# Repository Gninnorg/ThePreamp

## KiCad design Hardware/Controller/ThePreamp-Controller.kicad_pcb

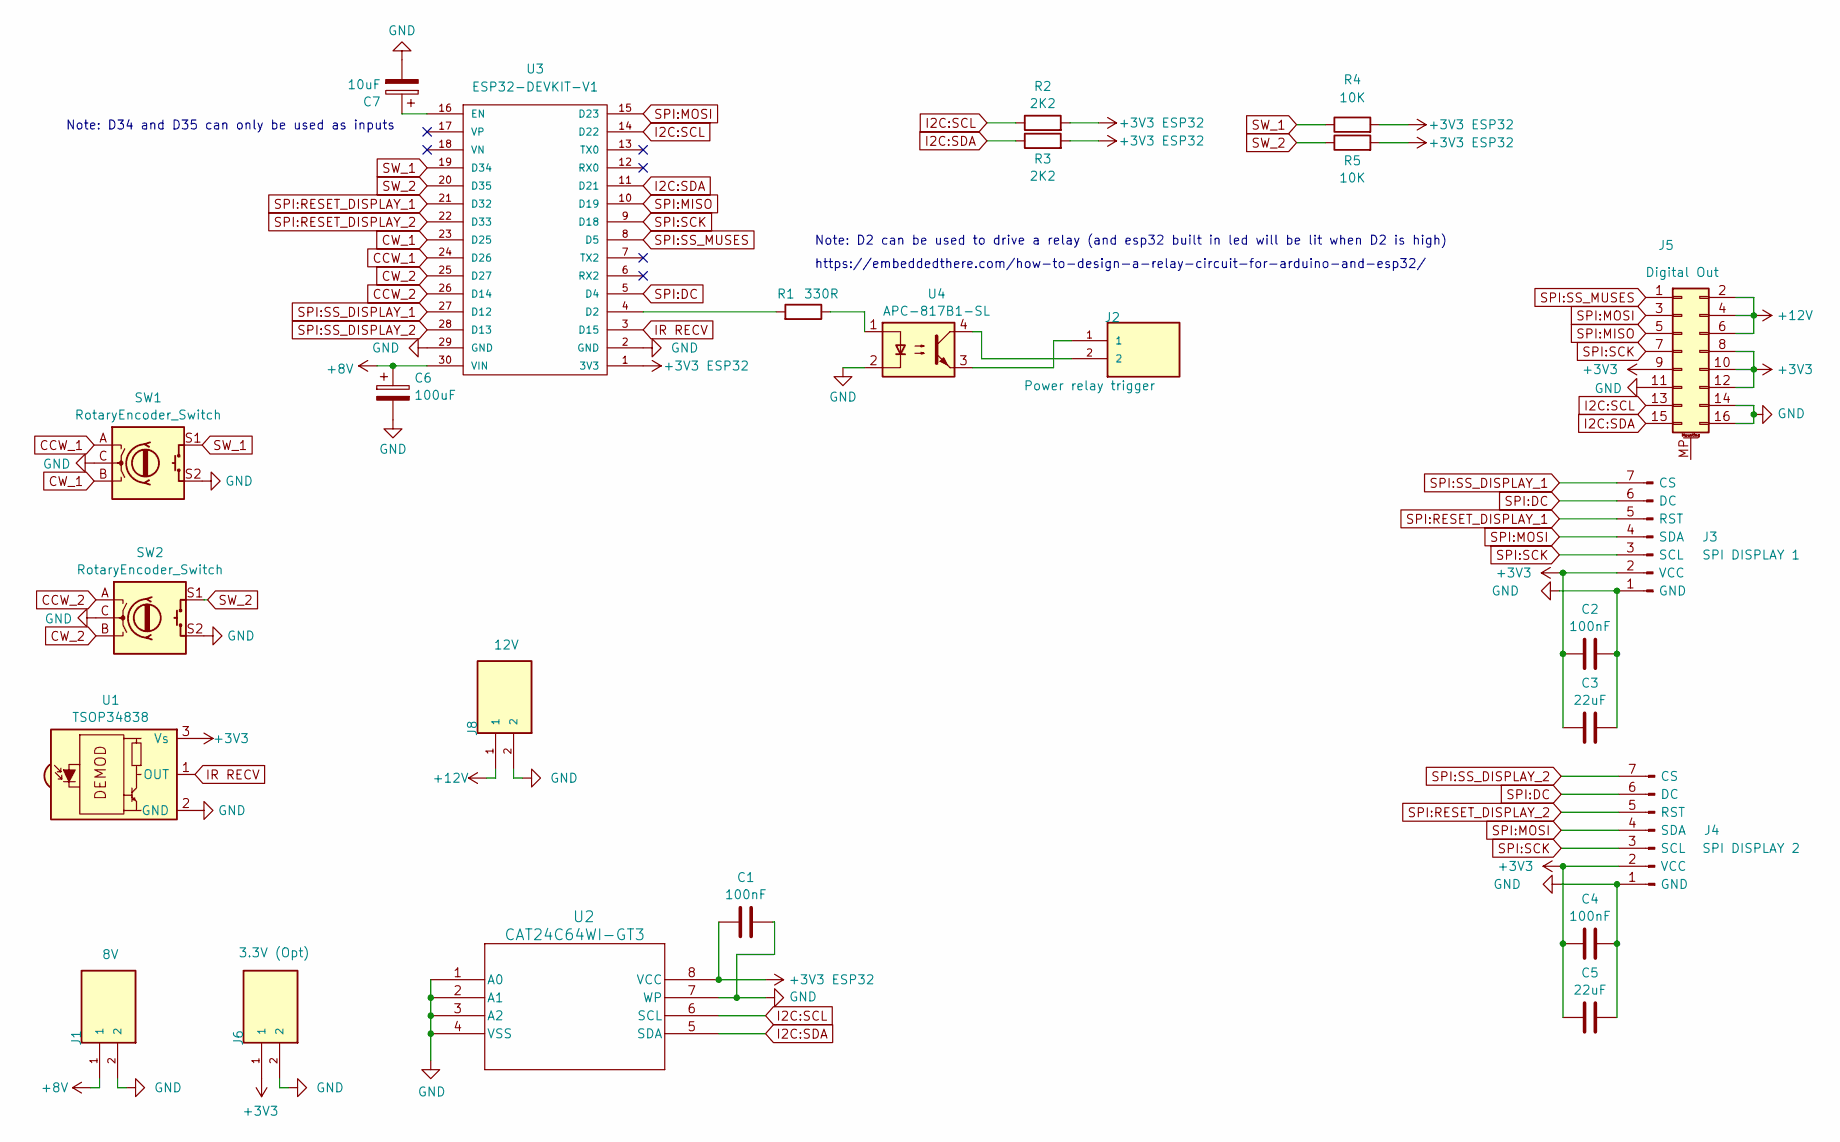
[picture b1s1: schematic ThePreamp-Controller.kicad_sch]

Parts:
C1, C2, C4: 100nF; C_0805_2012Metric_Pad1.18x1.45mm_HandSolder
C3, C5: 22uF; C_1206_3216Metric_Pad1.33x1.80mm_HandSolder
C6: 100uF; CP_Radial_D8.0mm_P3.50mm
C7: 10uF; CP_Radial_D8.0mm_P3.50mm
J1: 8V; TBP01R2-508-02BK (VERT)
J2: Power relay trigger; TBP01R2-508-02BK (VERT)
J3: SPI DISPLAY 1; OLED SPI 2.08
J4: SPI DISPLAY 2; OLED SPI 2.08
J5: Digital Out; IDC-Header_2x08_P2.54mm_Vertical
J6: 3.3V (Opt); TBP01R2-508-02BK (VERT)
J8: 12V; TBP01R2-508-02BK (VERT)
R1: 330R; R_0805_2012Metric_Pad1.20x1.40mm_HandSolder
R2, R3: 2K2; R_0805_2012Metric_Pad1.20x1.40mm_HandSolder
R4, R5: 10K; R_0805_2012Metric_Pad1.20x1.40mm_HandSolder
SW1, SW2: RotaryEncoder_Switch; RotaryEncoder_Alps_EC11E-Switch_Vertical_H20mm
U1: TSOP34838; Vishay_MOLD-3Pin
U2: CAT24C64WI-GT3; SOIC8_ONS-M
U3: ESP32-DEVKIT-V1; MODULE_ESP32_DEVKIT_V1; PARTREV N/A
U4: APC-817B1-SL; APC-817xx-SL_AMB-M

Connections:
+3V3: C2.1, C3.1, C4.1, C5.1, J3.2 (VCC), J4.2 (VCC), J5.8, J5.9, J5.10, J5.12, J6.1, U1.3 (Vs)
+3V3 ESP32: C1.1, R2.2, R3.2, R4.2, R5.2, U2.8 (VCC), U3.1 (3V3)
+8V: C6.1, J1.1, U3.30 (VIN)
+12V: J5.2, J5.4, J5.6, J8.1
CCW_1: SW1.A, U3.24 (D26)
CCW_2: SW2.A, U3.26 (D14)
CW_1: SW1.B, U3.23 (D25)
CW_2: SW2.B, U3.25 (D27)
GND: C1.2, C2.2, C3.2, C4.2, C5.2, C6.2, C7.2, J1.2, J3.1 (GND), J4.1 (GND), J5.11, J5.14, J5.16, J6.2, J8.2, SW1.C, SW1.S2, SW2.C, SW2.S2, U1.2 (GND), U2.1 (A0), U2.2 (A1), U2.3 (A2), U2.4 (VSS), U2.7 (WP), U3.2 (GND), U3.29 (GND), U4.2
I2C:SCL: J5.13, R2.1, U2.6 (SCL), U3.14 (D22)
I2C:SDA: J5.15, R3.1, U2.5 (SDA), U3.11 (D21)
IR RECV: U1.1 (OUT), U3.3 (D15)
unnamed: J2.1, U4.3
unnamed: J2.2, U4.4
unnamed: R1.1, U4.1
unnamed: R1.2, U3.4 (D2)
unnamed: C7.1, U3.16 (EN)
SPI:DC: J3.6 (DC), J4.6 (DC), U3.5 (D4)
SPI:MISO: J5.5, U3.10 (D19)
SPI:MOSI: J3.4 (SDA), J4.4 (SDA), J5.3, U3.15 (D23)
SPI:RESET_DISPLAY_1: J3.5 (RST), U3.21 (D32)
SPI:RESET_DISPLAY_2: J4.5 (RST), U3.22 (D33)
SPI:SCK: J3.3 (SCL), J4.3 (SCL), J5.7, U3.9 (D18)
SPI:SS_DISPLAY_1: J3.7 (CS), U3.27 (D12)
SPI:SS_DISPLAY_2: J4.7 (CS), U3.28 (D13)
SPI:SS_MUSES: J5.1, U3.8 (D5)
SW_1: R4.1, SW1.S1, U3.19 (D34)
SW_2: R5.1, SW2.S1, U3.20 (D35)

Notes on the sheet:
Note: D34 and D35 can only be used as inputs
https://embeddedthere.com/how-to-design-a-relay-circuit-for-arduino-and-esp32/
Note: D2 can be used to drive a relay (and esp32 built in led will be lit when D2 is high)

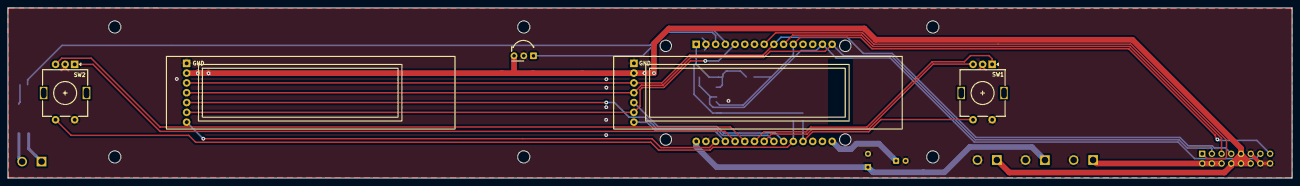
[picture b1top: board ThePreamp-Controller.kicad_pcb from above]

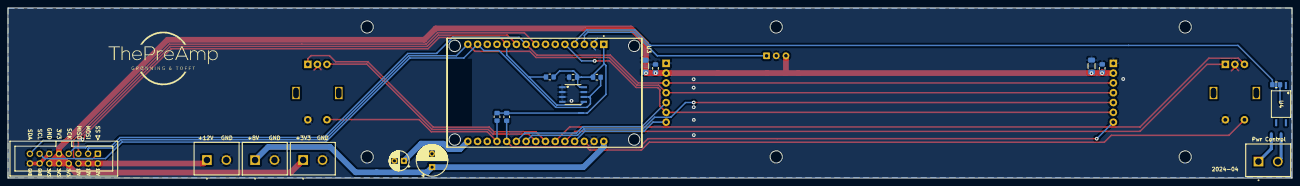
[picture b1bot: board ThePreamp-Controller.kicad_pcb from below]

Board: 2 copper layers, 335.9 x 44.5 mm, 31 parts (20 on the bottom side), 28 nets.

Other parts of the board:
 : MountingHole_3.2mm_M3_ISO7380
 #2,  #3,  #4,  #5,  #6: MountingHole_3.2mm_M3_ISO7380

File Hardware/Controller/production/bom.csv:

Designator,Footprint,Quantity,Value,LCSC Part #
"C1, C2, C4",0805,3,100nF,
"C3, C5",1206,2,22uF,
C6,CP_Radial_D8.0mm_P3.50mm,1,100uF,
J1,TBP01R2-508-02BK (VERT),1,8V,
J2,TBP01R2-508-02BK (VERT),1,Power relay trigger,
J3,OLED SPI 2.08,1,SPI DISPLAY 1,
J4,OLED SPI 2.08,1,SPI DISPLAY 2,
J5,IDC-Header_2x08_P2.54mm_Vertical,1,Digital Out,
J6,TBP01R2-508-02BK (VERT),1,3.3V (Opt),
J8,TBP01R2-508-02BK (VERT),1,12V,
R1,0805,1,330R,
"R2, R3",0805,2,2K2,
"SW1, SW2",RotaryEncoder_Alps_EC11E-Switch_Vertical_H20mm,2,RotaryEncoder_Switch,
U1,Vishay_MOLD-3Pin,1,TSOP34838,
U2,SOIC8_ONS-M,1,CAT24C64WI-GT3,
U3,MODULE_ESP32_DEVKIT_V1,1,ESP32-DEVKIT-V1,
U4,DIP-4_W7.62mm,1,APC-817B1-SL,

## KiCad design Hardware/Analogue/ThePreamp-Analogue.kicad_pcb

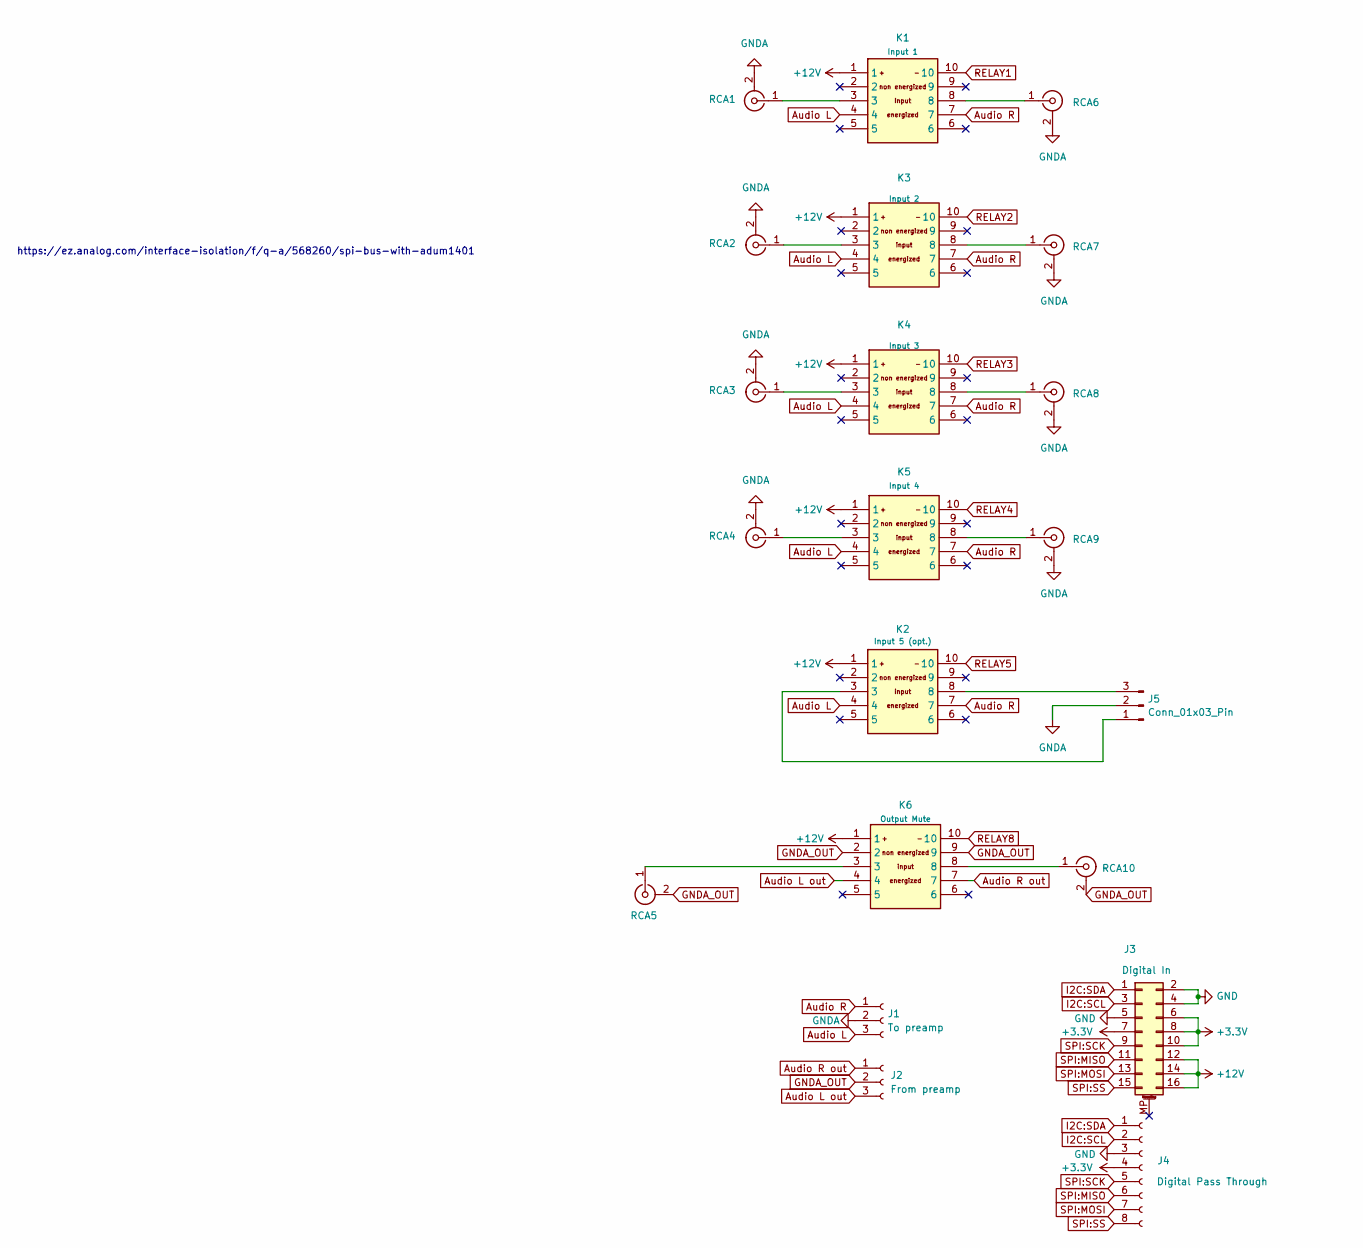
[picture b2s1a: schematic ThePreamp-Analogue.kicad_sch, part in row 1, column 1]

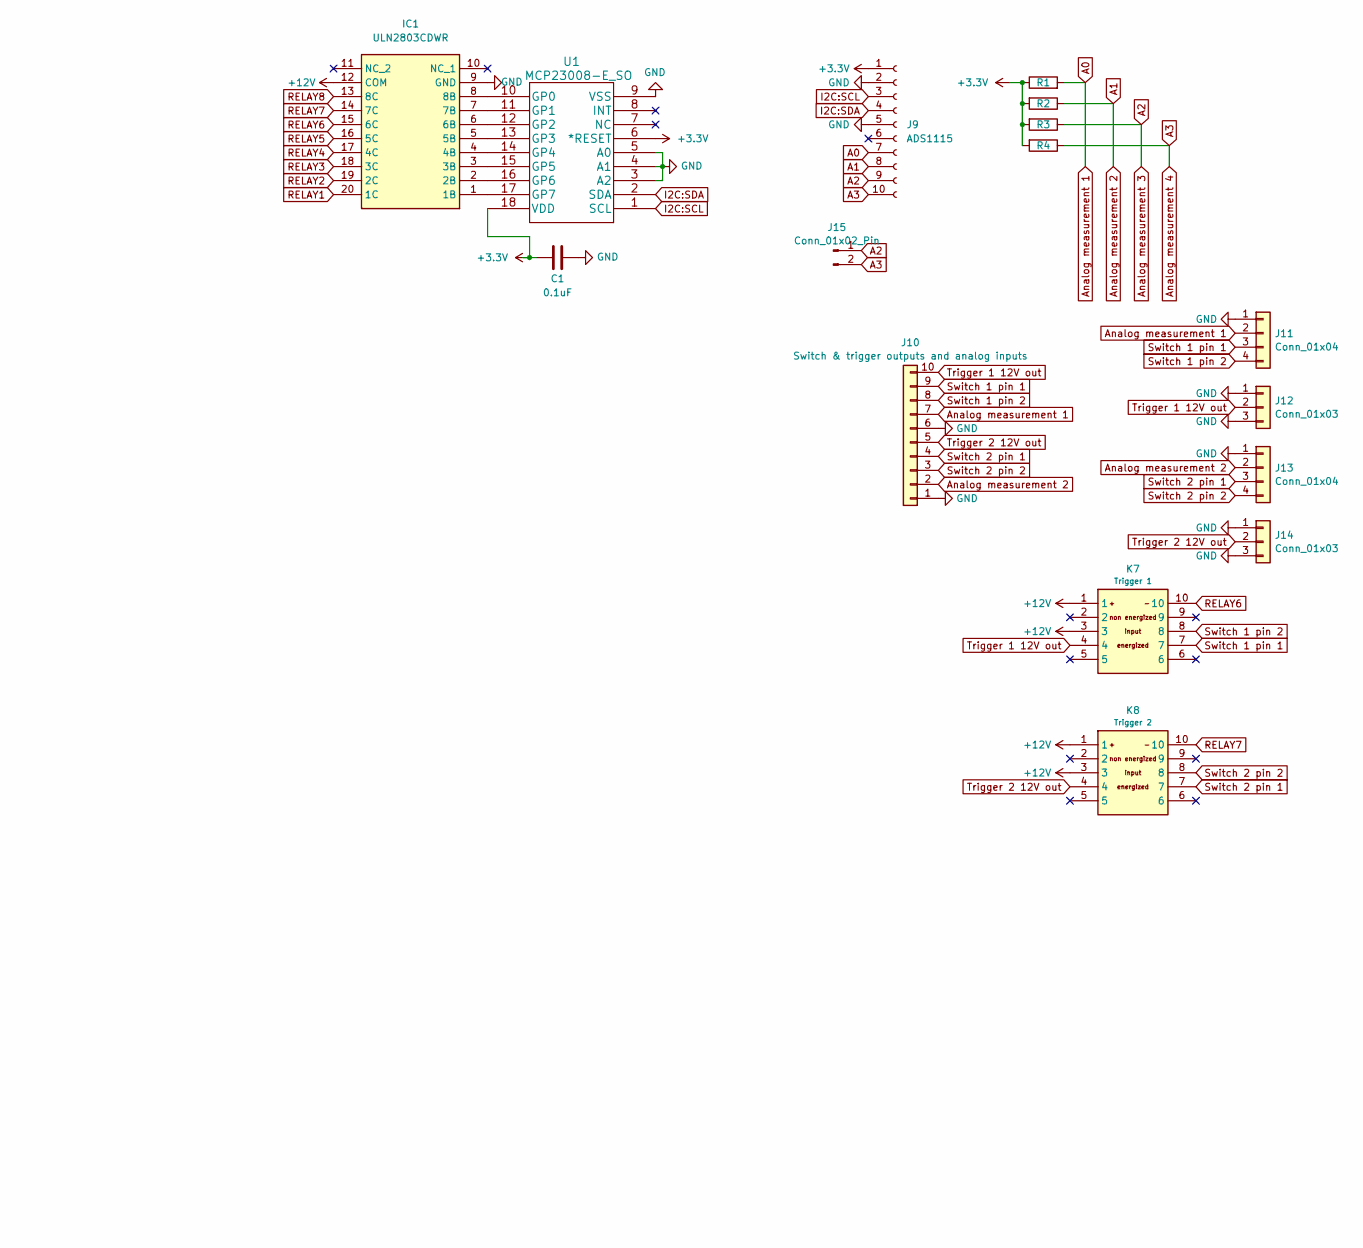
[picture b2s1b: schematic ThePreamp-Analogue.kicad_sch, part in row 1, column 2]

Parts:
C1: 0.1uF; C_0805_2012Metric_Pad1.18x1.45mm_HandSolder
IC1: ULN2803CDWR; SOIC127P1030X265-20N; Mouser Part Number 595-ULN2803CDWR
J1: To preamp; PinSocket_1x03_P2.54mm_Vertical
J2: From preamp; PinSocket_1x03_P2.54mm_Vertical
J3: Digital In; IDC-Header_2x08_P2.54mm_Vertical
J4: Digital Pass Through; PinSocket_1x08_P2.54mm_Vertical
J5: Conn_01x03_Pin; PinHeader_1x03_P2.54mm_Vertical
J9: ADS1115; PinHeader_1x10_P2.54mm_Vertical
J10: Switch & trigger outputs and analog inputs; PinSocket_1x10_P2.54mm_Vertical
J11, J13: Conn_01x04; M8 4 pin
J12, J14: Conn_01x03; M8 3 pin
J15: Conn_01x02_Pin; PinHeader_1x02_P2.54mm_Vertical
K1: Input 1; DIPS762W60P254L1420H630Q10N; Manufacturer_Part_Number EA2-12NJ; Mouser Part Number 551-EA2-12NJ
K2: Input 5 (opt.); DIPS762W60P254L1420H630Q10N; Manufacturer_Part_Number EA2-12NJ; Mouser Part Number 551-EA2-12NJ
K3: Input 2; DIPS762W60P254L1420H630Q10N; Manufacturer_Part_Number EA2-12NJ; Mouser Part Number 551-EA2-12NJ
K4: Input 3; DIPS762W60P254L1420H630Q10N; Manufacturer_Part_Number EA2-12NJ; Mouser Part Number 551-EA2-12NJ
K5: Input 4; DIPS762W60P254L1420H630Q10N; Manufacturer_Part_Number EA2-12NJ; Mouser Part Number 551-EA2-12NJ
K6: Output Mute; DIPS762W60P254L1420H630Q10N; Manufacturer_Part_Number EA2-12NJ; Mouser Part Number 551-EA2-12NJ
K7: Trigger 1; DIPS762W60P254L1420H630Q10N; Manufacturer_Part_Number EA2-12NJ; Mouser Part Number 551-EA2-12NJ
K8: Trigger 2; DIPS762W60P254L1420H630Q10N; Manufacturer_Part_Number EA2-12NJ; Mouser Part Number 551-EA2-12NJ
R1, R2, R3, R4: 10K; R_0805_2012Metric_Pad1.20x1.40mm_HandSolder
RCA1, RCA2, RCA3, RCA4, RCA5, RCA6, RCA7, RCA8, RCA9, RCA10: RCA_Connector_ALI; RCA Connector ALI
U1: MCP23008-E_SO; SOIC127P1030X265-18N

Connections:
+3.3V: C1.1, J3.6, J3.7, J3.8, J3.10, J4.4, J9.1, R1.1, R2.2, R3.2, R4.2, U1.6 (*RESET), U1.18 (VDD)
+12V: IC1.12 (COM), J3.12, J3.14, J3.16, K1.1, K2.1, K3.1, K4.1, K5.1, K6.1, K7.1, K7.3, K8.1, K8.3
A0: J9.7, J10.7, J11.2, R1.2
A1: J9.8, J10.2, J13.2, R2.1
A2: J9.9, J15.1, R3.1
A3: J9.10, J15.2, R4.1
Audio L: J1.3, K1.4, K2.4, K3.4, K4.4, K5.4
Audio L out: J2.3, K6.4
Audio R: J1.1, K1.7, K2.7, K3.7, K4.7, K5.7
Audio R out: J2.1, K6.7
GND: C1.2, IC1.9 (GND), J3.2, J3.4, J3.5, J4.3, J9.2, J9.5, J10.1, J10.6, J11.1, J12.1, J12.3, J13.1, J14.1, J14.3, U1.3 (A2), U1.4 (A1), U1.5 (A0), U1.9 (VSS)
GNDA: J1.2, J5.2, RCA1.2 (Ext), RCA2.2 (Ext), RCA3.2 (Ext), RCA4.2 (Ext), RCA6.2 (Ext), RCA7.2 (Ext), RCA8.2 (Ext), RCA9.2 (Ext)
GNDA_OUT: J2.2, K6.2, K6.9, RCA5.2 (Ext), RCA10.2 (Ext)
I2C:SCL: J3.3, J4.2, J9.3, U1.1 (SCL)
I2C:SDA: J3.1, J4.1, J9.4, U1.2 (SDA)
unnamed: IC1.1 (1B), U1.17 (GP7)
unnamed: IC1.2 (2B), U1.16 (GP6)
unnamed: IC1.3 (3B), U1.15 (GP5)
unnamed: IC1.4 (4B), U1.14 (GP4)
unnamed: IC1.5 (5B), U1.13 (GP3)
unnamed: IC1.6 (6B), U1.12 (GP2)
unnamed: IC1.7 (7B), U1.11 (GP1)
unnamed: IC1.8 (8B), U1.10 (GP0)
unnamed: J5.1, K2.3
unnamed: J5.3, K2.8
unnamed: K1.3, RCA1.1 (In)
unnamed: K3.3, RCA2.1 (In)
unnamed: K4.3, RCA3.1 (In)
unnamed: K5.3, RCA4.1 (In)
unnamed: K6.3, RCA5.1 (In)
unnamed: K1.8, RCA6.1 (In)
unnamed: K3.8, RCA7.1 (In)
unnamed: K4.8, RCA8.1 (In)
unnamed: K5.8, RCA9.1 (In)
unnamed: K6.8, RCA10.1 (In)
RELAY1: IC1.20 (1C), K1.10
RELAY2: IC1.19 (2C), K3.10
RELAY3: IC1.18 (3C), K4.10
RELAY4: IC1.17 (4C), K5.10
RELAY5: IC1.16 (5C), K2.10
RELAY6: IC1.15 (6C), K7.10
RELAY7: IC1.14 (7C), K8.10
RELAY8: IC1.13 (8C), K6.10
SPI:MISO: J3.11, J4.6
SPI:MOSI: J3.13, J4.7
SPI:SCK: J3.9, J4.5
SPI:SS: J3.15, J4.8
Switch 1 pin 1: J10.9, J11.3, K7.7
Switch 1 pin 2: J10.8, J11.4, K7.8
Switch 2 pin 1: J10.4, J13.3, K8.7
Switch 2 pin 2: J10.3, J13.4, K8.8
Trigger 1 12V out: J10.10, J12.2, K7.4
Trigger 2 12V out: J10.5, J14.2, K8.4

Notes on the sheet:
https://ez.analog.com/interface-isolation/f/q-a/568260/spi-bus-with-adum1401

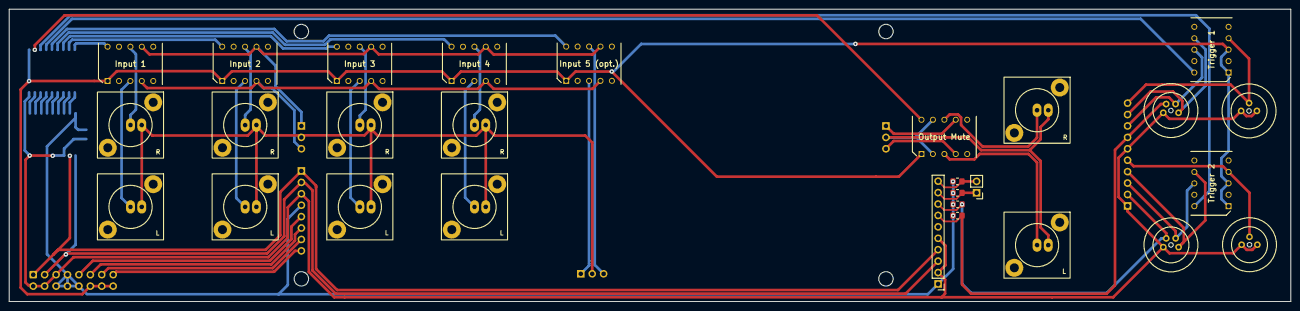
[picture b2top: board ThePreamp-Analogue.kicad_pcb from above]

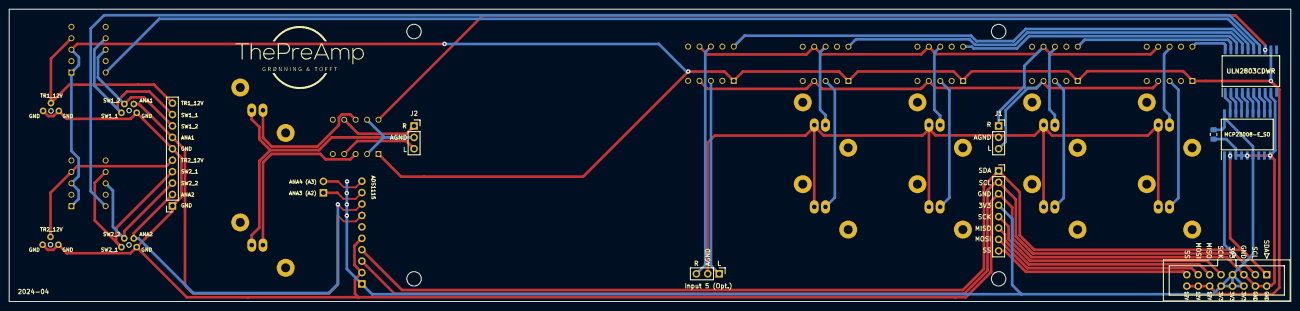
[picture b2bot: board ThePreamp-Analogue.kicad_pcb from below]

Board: 2 copper layers, 285.0 x 65.0 mm, 37 parts (9 on the bottom side), 53 nets.

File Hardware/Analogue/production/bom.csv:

Designator,Footprint,Quantity,Value,LCSC Part #
C1,0805,1,0.1uF,
IC1,SOIC127P1030X265-20N,1,ULN2803CDWR,
J1,PinSocket_1x03_P2.54mm_Vertical,1,To preamp,
J10,PinSocket_1x10_P2.54mm_Vertical,1,Switch & trigger outputs and analog inputs,
"J11, J13",M8 4 pin,2,Conn_01x04,
"J12, J14",M8 3 pin,2,Conn_01x03,
J15,PinHeader_1x02_P2.54mm_Vertical,1,Conn_01x02_Pin,
J2,PinSocket_1x03_P2.54mm_Vertical,1,From preamp,
J3,IDC-Header_2x08_P2.54mm_Vertical,1,Digital In,
J4,PinSocket_1x08_P2.54mm_Vertical,1,Digital Pass Through,
J5,PinHeader_1x03_P2.54mm_Vertical,1,Conn_01x03_Pin,
J9,PinHeader_1x10_P2.54mm_Vertical,1,ADS1115,
K1,DIPS762W60P254L1420H630Q10N,1,Input 1,
K2,DIPS762W60P254L1420H630Q10N,1,Input 5 (opt.),
K3,DIPS762W60P254L1420H630Q10N,1,Input 2,
K4,DIPS762W60P254L1420H630Q10N,1,Input 3,
K5,DIPS762W60P254L1420H630Q10N,1,Input 4,
K6,DIPS762W60P254L1420H630Q10N,1,Output Mute,
K7,DIPS762W60P254L1420H630Q10N,1,Trigger 1,
K8,DIPS762W60P254L1420H630Q10N,1,Trigger 2,
"R1, R2, R3, R4",0805,4,10K,
"RCA1, RCA10, RCA2, RCA3, RCA4, RCA5, RCA6, RCA7, RCA8, RCA9",RCA Connector ALI,10,RCA_Connector_ALI,
U1,SOIC127P1030X265-18N,1,MCP23008-E_SO,

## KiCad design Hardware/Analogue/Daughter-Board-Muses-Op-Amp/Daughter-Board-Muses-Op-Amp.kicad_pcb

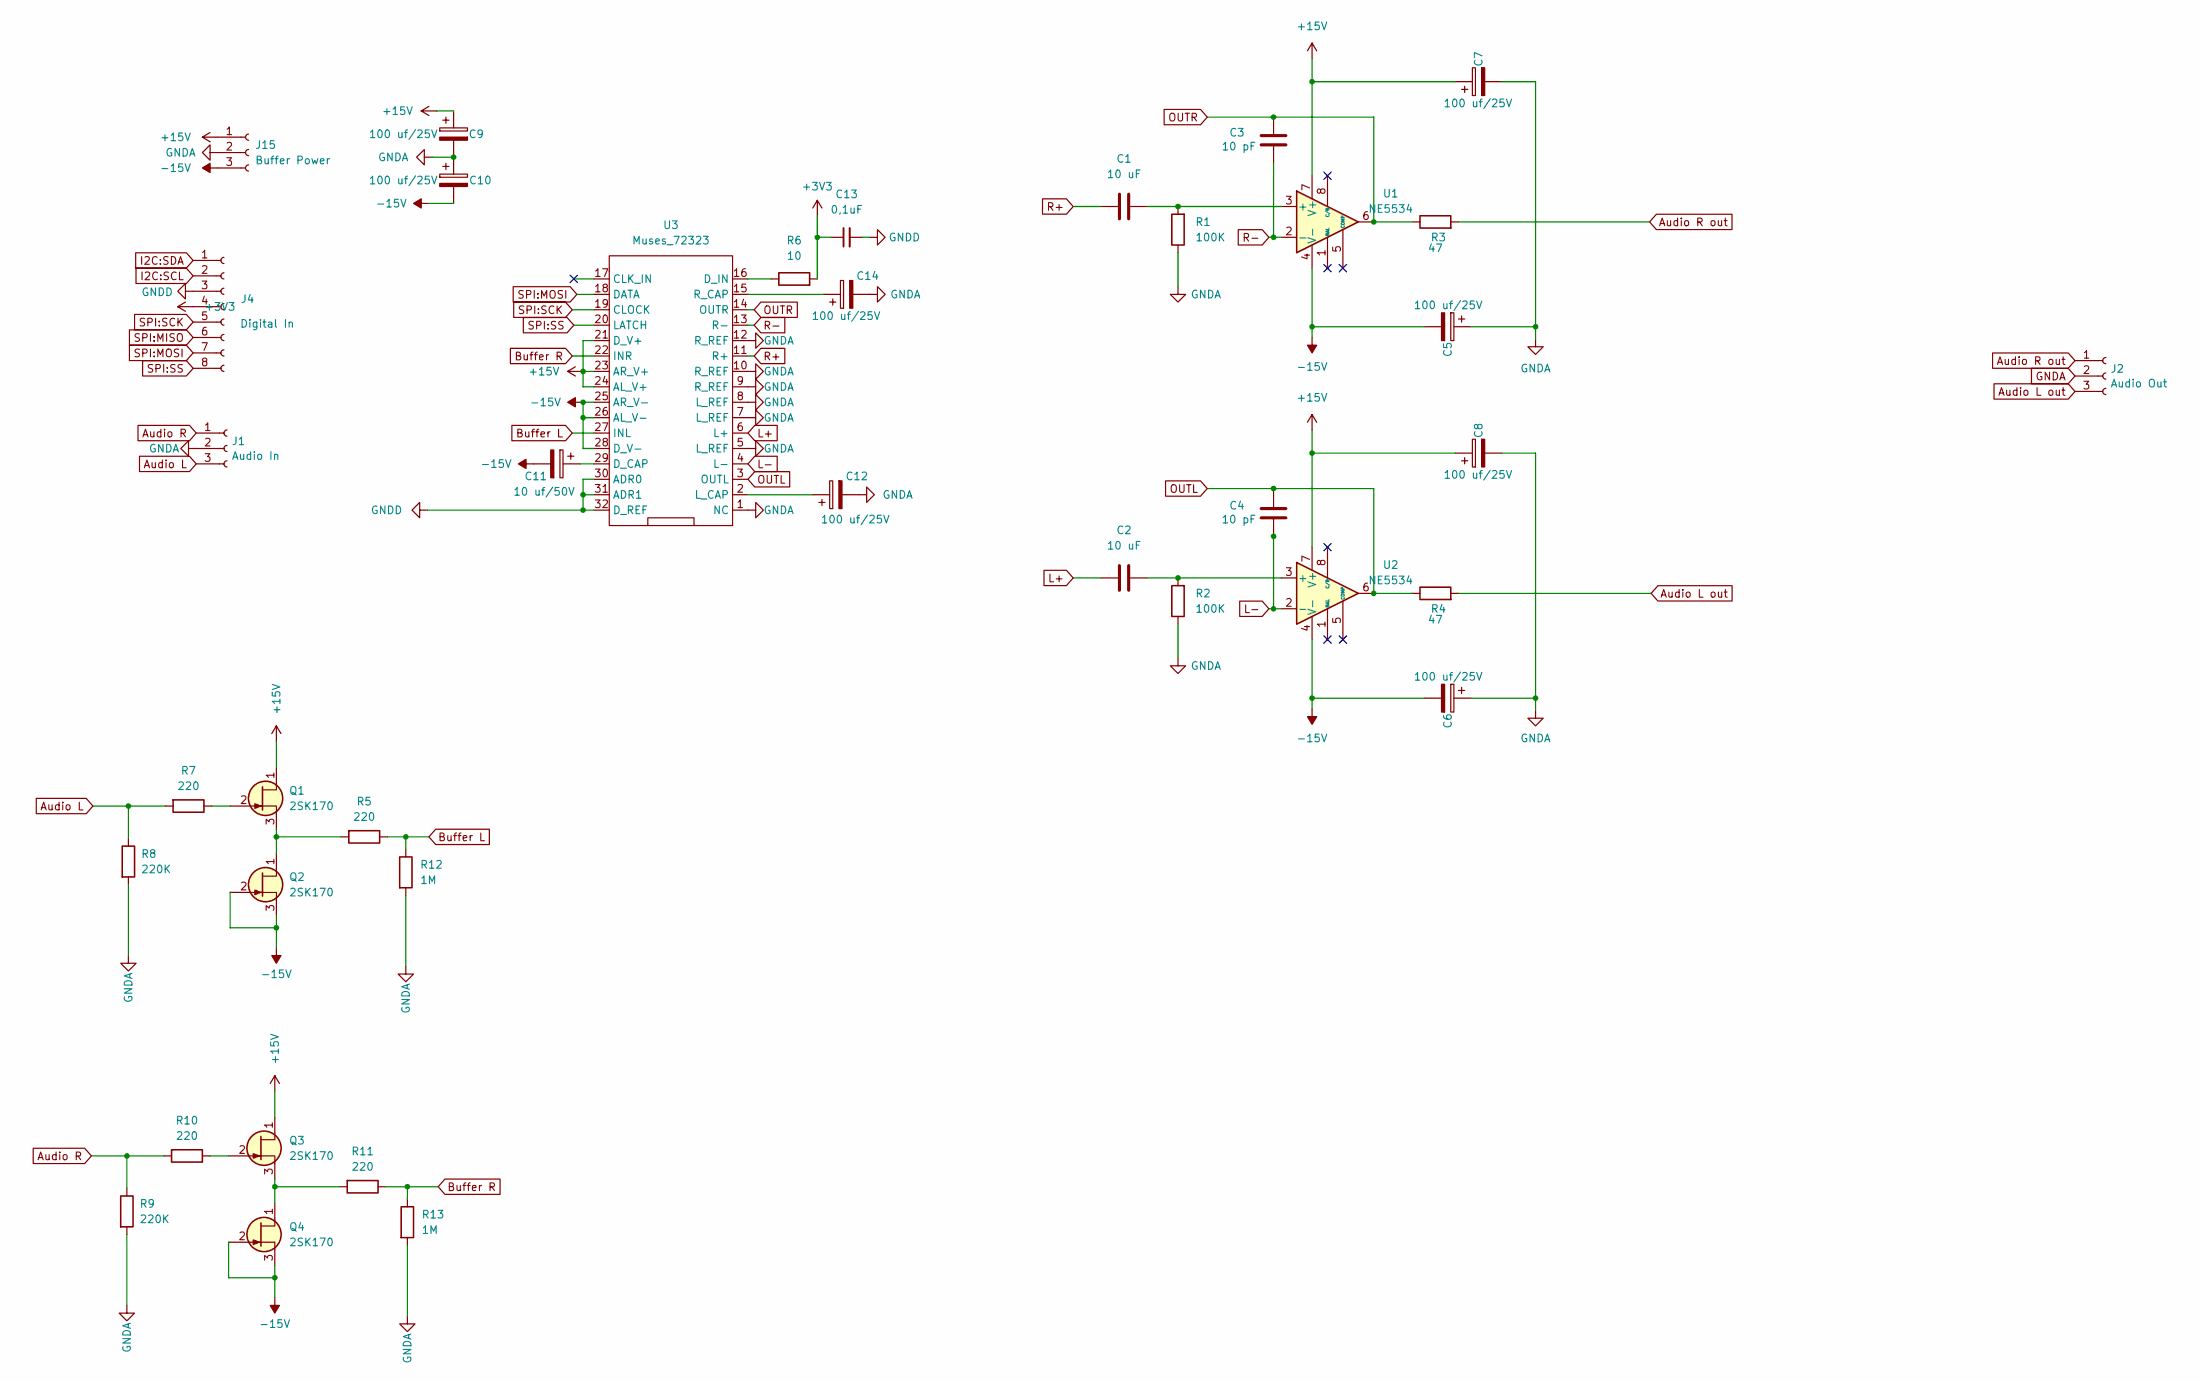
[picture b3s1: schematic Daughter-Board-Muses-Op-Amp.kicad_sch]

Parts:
C1, C2: 10 uF; CP_Radial_D5.0mm_P2.00mm
C3, C4: 10 pF; C_0805_2012Metric_Pad1.18x1.45mm_HandSolder
C5, C6, C7, C8, C9, C10, C12, C14: 100 uf/25V; CP_Radial_D8.0mm_P3.50mm
C11: 10 uf/50V; CP_Radial_D5.0mm_P2.00mm
C13: 0,1uF; C_0805_2012Metric_Pad1.18x1.45mm_HandSolder
J1: Audio In; PinHeader_1x03_P2.54mm_Vertical
J2: Audio Out; PinHeader_1x03_P2.54mm_Vertical
J4: Digital In; PinHeader_1x08_P2.54mm_Vertical
J15: Buffer Power; PinHeader_1x03_P2.54mm_Vertical
Q1, Q2, Q3, Q4: 2SK170; TO-92_HandSolder
R1, R2: 100K; R_0805_2012Metric_Pad1.20x1.40mm_HandSolder
R3, R4: 47; R_0805_2012Metric_Pad1.20x1.40mm_HandSolder
R5, R7, R10, R11: 220; R_0805_2012Metric_Pad1.20x1.40mm_HandSolder
R6: 10; R_0805_2012Metric_Pad1.20x1.40mm_HandSolder
R8, R9: 220K; R_0805_2012Metric_Pad1.20x1.40mm_HandSolder
R12, R13: 1M; R_0805_2012Metric_Pad1.20x1.40mm_HandSolder
U1, U2: NE5534; DIP-8_W7.62mm_Socket_LongPads
U3: Muses_72323; TSSOP-32_6.1x11mm_P0.65mm

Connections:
+3V3: C13.1, J4.4, R6.2
+15V: C7.1, C8.1, C9.1, J15.1, Q1.1 (D), Q3.1 (D), U1.7 (V+), U2.7 (V+), U3.21 (D_V+), U3.23 (AR_V+), U3.24 (AL_V+)
-15V: C5.2, C6.2, C10.2, C11.2, J15.3, Q2.2 (G), Q2.3 (S), Q4.2 (G), Q4.3 (S), U1.4 (V-), U2.4 (V-), U3.25 (AR_V-), U3.26 (AL_V-), U3.28 (D_V-)
Audio L: J1.3, R7.2, R8.1
Audio L out: J2.3, R4.2
Audio R: J1.1, R9.1, R10.2
Audio R out: J2.1, R3.2
Buffer L: R5.1, R12.1, U3.27 (INL)
Buffer R: R11.1, R13.1, U3.22 (INR)
GNDA: C5.1, C6.1, C7.2, C8.2, C9.2, C10.1, C12.2, C14.2, J1.2, J2.2, J15.2, R1.1, R2.1, R8.2, R9.2, R12.2, R13.2, U3.1 (NC), U3.5 (L_REF), U3.7 (L_REF), U3.8 (L_REF), U3.9 (R_REF), U3.10 (R_REF), U3.12 (R_REF)
GNDD: C13.2, J4.3, U3.30 (ADR0), U3.31 (ADR1), U3.32 (D_REF)
I2C:SCL: J4.2
I2C:SDA: J4.1
L+: C2.1, U3.6 (L+)
L-: C4.2, U2.2 (-), U3.4 (L-)
unnamed: Q1.2 (G), R7.1
unnamed: Q1.3 (S), Q2.1 (D), R5.2
unnamed: Q3.2 (G), R10.1
unnamed: Q3.3 (S), Q4.1 (D), R11.2
unnamed: C1.2, R1.2, U1.3 (+)
unnamed: C2.2, R2.2, U2.3 (+)
unnamed: C11.1, U3.29 (D_CAP)
unnamed: R6.1, U3.16 (D_IN)
unnamed: C12.1, U3.2 (L_CAP)
unnamed: C14.1, U3.15 (R_CAP)
OUTL: C4.1, R4.1, U2.6, U3.3 (OUTL)
OUTR: C3.1, R3.1, U1.6, U3.14 (OUTR)
R+: C1.1, U3.11 (R+)
R-: C3.2, U1.2 (-), U3.13 (R-)
SPI:MISO: J4.6
SPI:MOSI: J4.7, U3.18 (DATA)
SPI:SCK: J4.5, U3.19 (CLOCK)
SPI:SS: J4.8, U3.20 (LATCH)

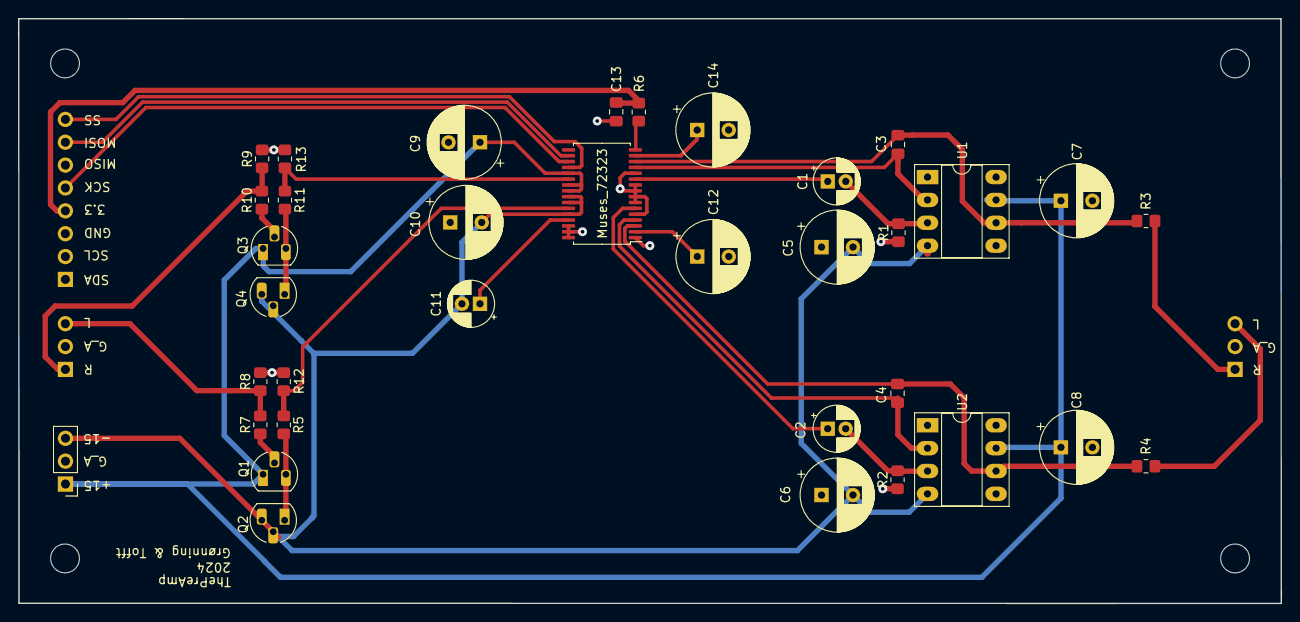
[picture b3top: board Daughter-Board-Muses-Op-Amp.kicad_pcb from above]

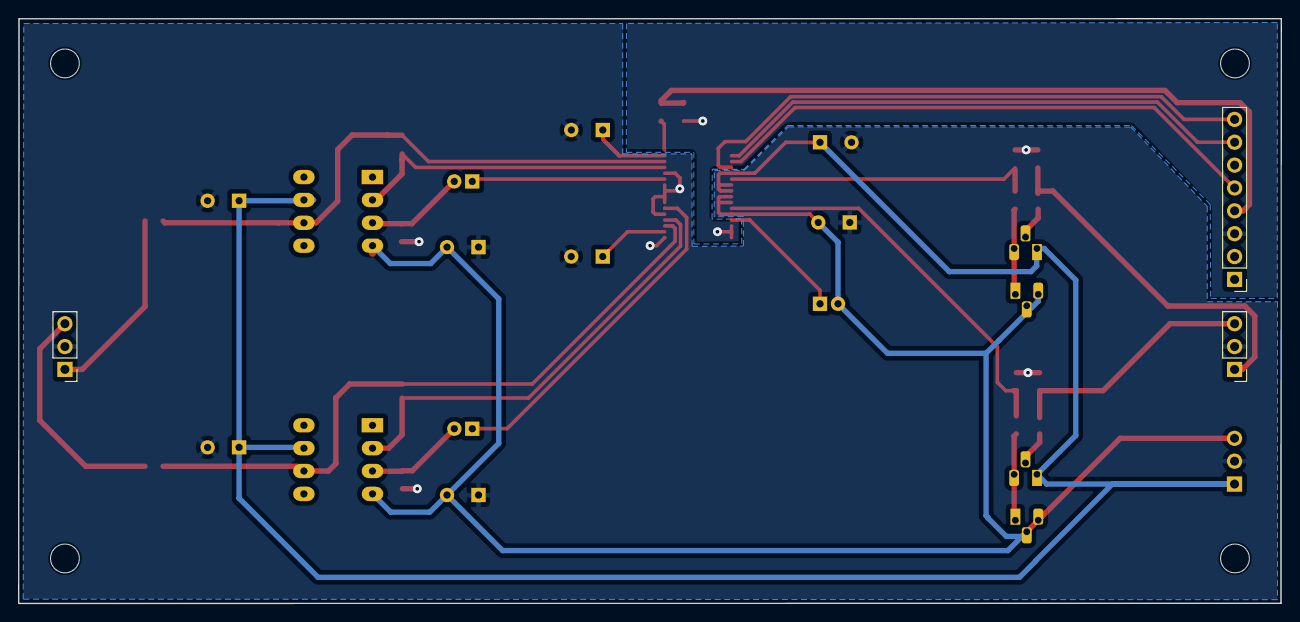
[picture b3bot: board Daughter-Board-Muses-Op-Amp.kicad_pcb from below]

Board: 2 copper layers, 140.3 x 65.0 mm, 38 parts (3 on the bottom side), 30 nets.

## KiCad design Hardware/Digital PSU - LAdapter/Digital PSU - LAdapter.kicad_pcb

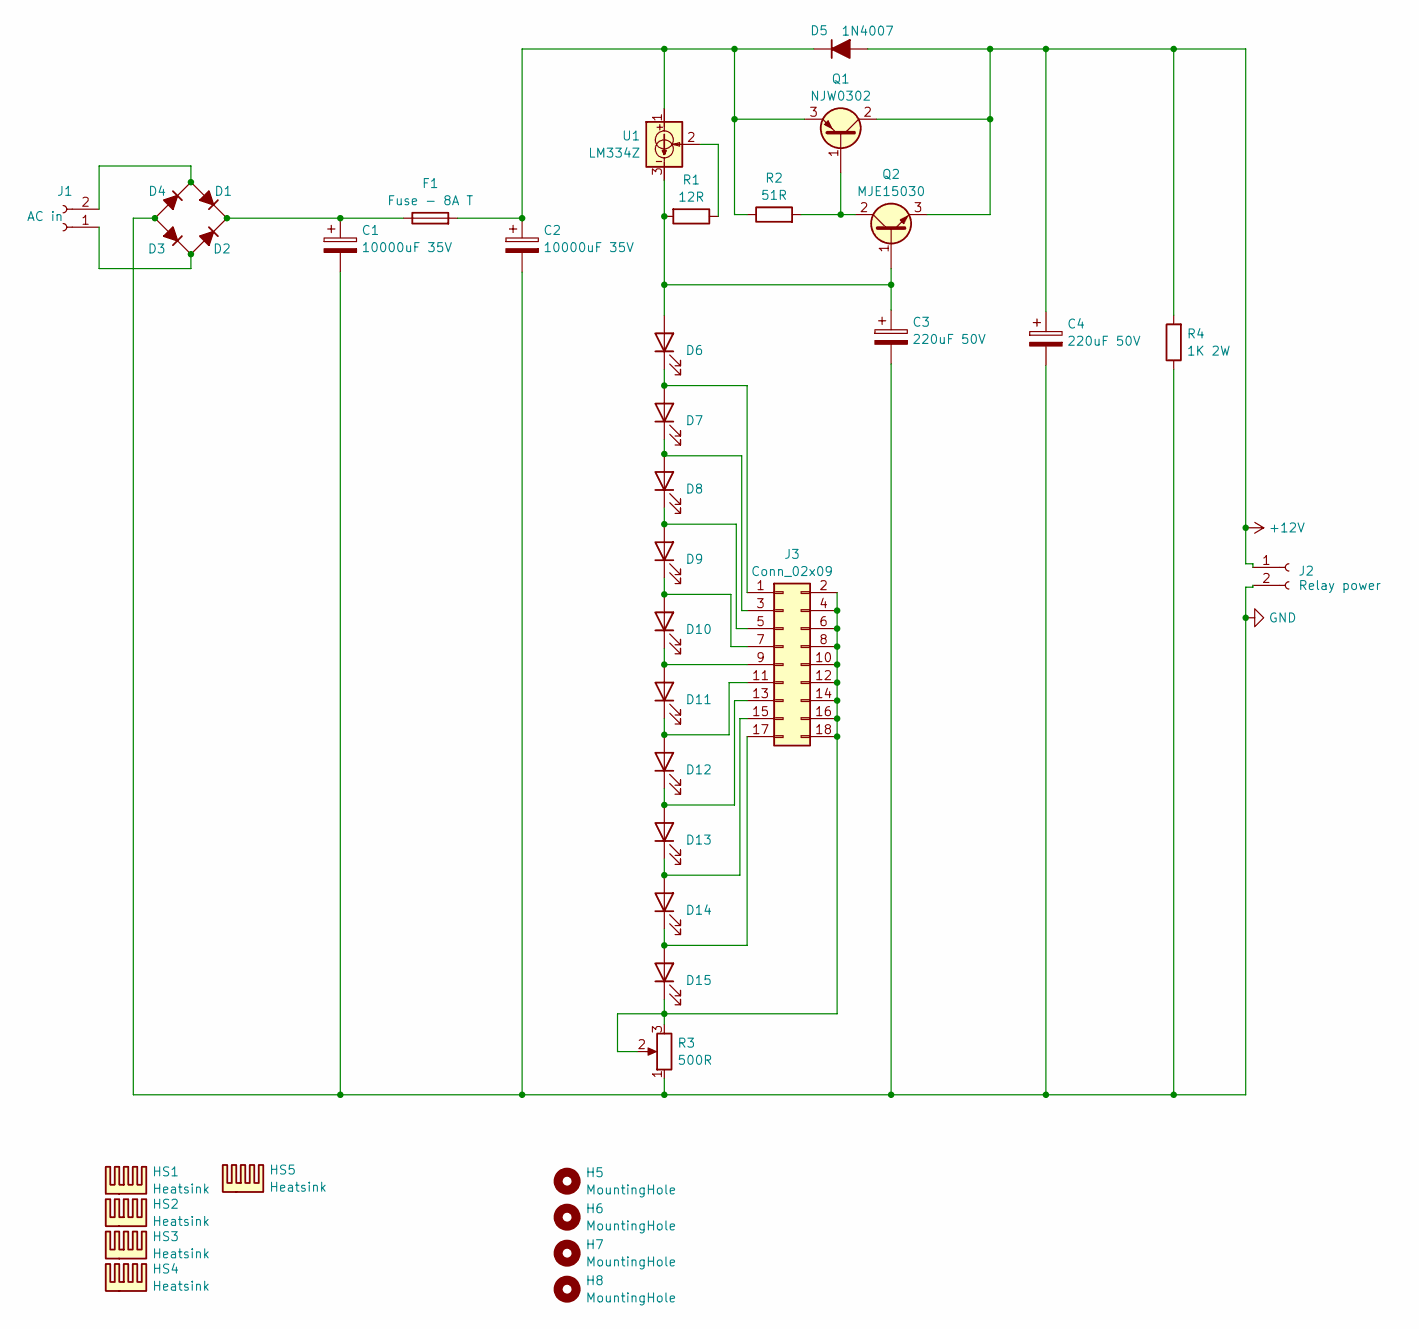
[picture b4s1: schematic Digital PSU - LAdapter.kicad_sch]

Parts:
C1, C2: 10000uF 35V; CP_Radial_D30.0mm_P10.00mm_SnapIn
C3, C4: 220uF 50V; CP_Radial_D10.0mm_P5.00mm
D1, D2, D3, D4: D_45deg_Filled; TO-220-2_Vertical
D5: 1N4007; D_DO-41_SOD81_P7.62mm_Horizontal
D6, D7, D8, D9, D10, D11, D12, D13, D14, D15: LED_Rectangular_W5.0mm_H2.0mm
F1: Fuse - 8A T; Keystone fuseholder 4527
H5, H6, H7, H8: MountingHole; MountingHole_3.2mm_M3_DIN965
HS1, HS2, HS3, HS4: Heatsink; Heatsink_Fischer_SK145-STS_29x12mm_2xDrill2.5mm
HS5: Heatsink; Heatsink_Fischer_SK129-STS_42x25mm_2xDrill2.5mm
J1: AC in; TBP01R1-508-02BK
J2: Relay power; TBP01R1-508-02BK
J3: Conn_02x09; PinHeader_2x09_P2.54mm_Vertical
Q1: NJW0302; TO-3P-3_Vertical_BCE
Q2: MJE15030; TO-220-3_Vertical_BCE
R1: 12R; R_Axial_DIN0207_L6.3mm_D2.5mm_P10.16mm_Horizontal
R2: 51R; R_Axial_DIN0207_L6.3mm_D2.5mm_P10.16mm_Horizontal
R3: 500R; Potentiometer_Bourns_3296W_Vertical
R4: 1K 2W; R_Axial_DIN0414_L11.9mm_D4.5mm_P15.24mm_Horizontal
U1: LM334Z; TO-92_Inline

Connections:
+12V: C4.1, D5.2 (A), J2.1, Q1.2 (C), Q2.3 (E), R4.2
GND: C1.2, C2.2, C3.2, C4.2, D3.2 (A), D4.2 (A), J2.2, R3.1, R4.1
unnamed: D1.2 (A), D4.1 (K), J1.2
unnamed: C1.1, D1.1 (K), D2.1 (K), F1.1
unnamed: D2.2 (A), D3.1 (K), J1.1
unnamed: C2.1, D5.1 (K), F1.2, Q1.3 (E), R2.1, U1.1
unnamed: C3.1, D6.2 (A), Q2.1 (B), R1.2, U1.3
unnamed: D6.1 (K), D7.2 (A), J3.1
unnamed: D7.1 (K), D8.2 (A), J3.3
unnamed: D8.1 (K), D9.2 (A), J3.5
unnamed: D9.1 (K), D10.2 (A), J3.7
unnamed: D10.1 (K), D11.2 (A), J3.9
unnamed: D11.1 (K), D12.2 (A), J3.11
unnamed: D12.1 (K), D13.2 (A), J3.13
unnamed: D13.1 (K), D14.2 (A), J3.15
unnamed: D14.1 (K), D15.2 (A), J3.17
unnamed: D15.1 (K), J3.2, J3.4, J3.6, J3.8, J3.10, J3.12, J3.14, J3.16, J3.18, R3.2, R3.3
unnamed: Q1.1 (B), Q2.2 (C), R2.2
unnamed: R1.1, U1.2

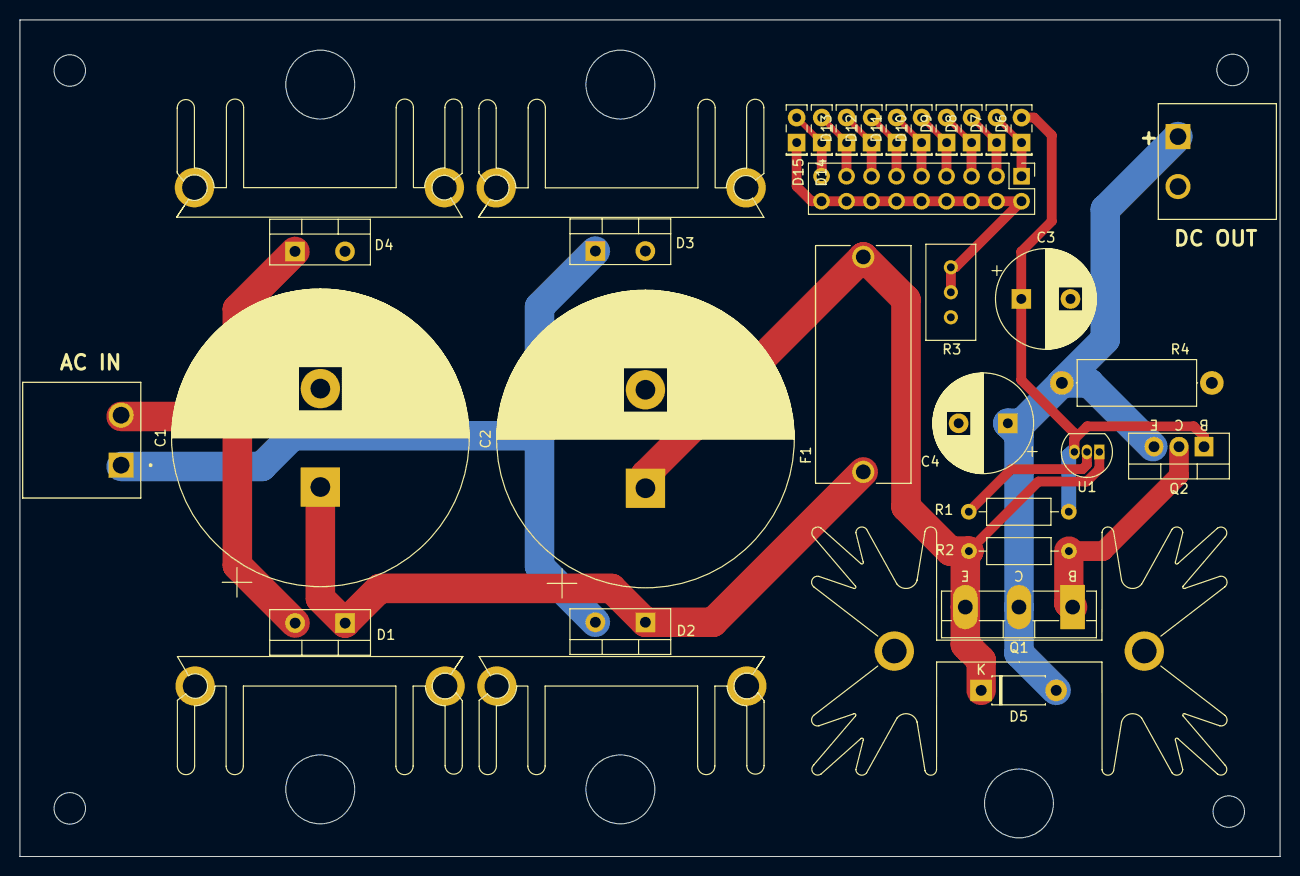
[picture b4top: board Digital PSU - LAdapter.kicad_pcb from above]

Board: 2 copper layers, 128.0 x 85.0 mm, 39 parts (0 on the bottom side), 19 nets.

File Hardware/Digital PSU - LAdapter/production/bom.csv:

Designator,Footprint,Quantity,Value,LCSC Part #
"C1, C2",CP_Radial_D30.0mm_P10.00mm_SnapIn,2,10000uF 35V,
"C3, C4",CP_Radial_D10.0mm_P5.00mm,2,220uF 50V,
"D1, D2, D3, D4",TO-220-2_Vertical,4,D_45deg_Filled,
"D10, D11, D12, D13, D14, D15, D6, D7, D8, D9",LED_Rectangular_W5.0mm_H2.0mm,10,~,
D5,D_DO-41_SOD81_P7.62mm_Horizontal,1,1N4007,
F1,Keystone fuseholder 4527,1,Fuse - 8A T,
"HS1, HS2, HS3, HS4",Heatsink_Fischer_SK145-STS_29x12mm_2xDrill2.5mm,4,Heatsink,
HS5,Heatsink_Fischer_SK129-STS_42x25mm_2xDrill2.5mm,1,Heatsink,
J1,TBP01R1-508-02BK,1,AC in,
J2,TBP01R1-508-02BK,1,Relay power,
J3,PinHeader_2x09_P2.54mm_Vertical,1,Conn_02x09,
Q1,TO-3P-3_Vertical_BCE,1,NJW0302,
Q2,TO-220-3_Vertical_BCE,1,MJE15030,
R1,R_Axial_DIN0207_L6.3mm_D2.5mm_P10.16mm_Horizontal,1,12R,
R2,R_Axial_DIN0207_L6.3mm_D2.5mm_P10.16mm_Horizontal,1,51R,
R3,Potentiometer_Bourns_3296W_Vertical,1,500R,
R4,R_Axial_DIN0414_L11.9mm_D4.5mm_P15.24mm_Horizontal,1,1K 2W,
U1,TO-92_Inline,1,LM334Z,
